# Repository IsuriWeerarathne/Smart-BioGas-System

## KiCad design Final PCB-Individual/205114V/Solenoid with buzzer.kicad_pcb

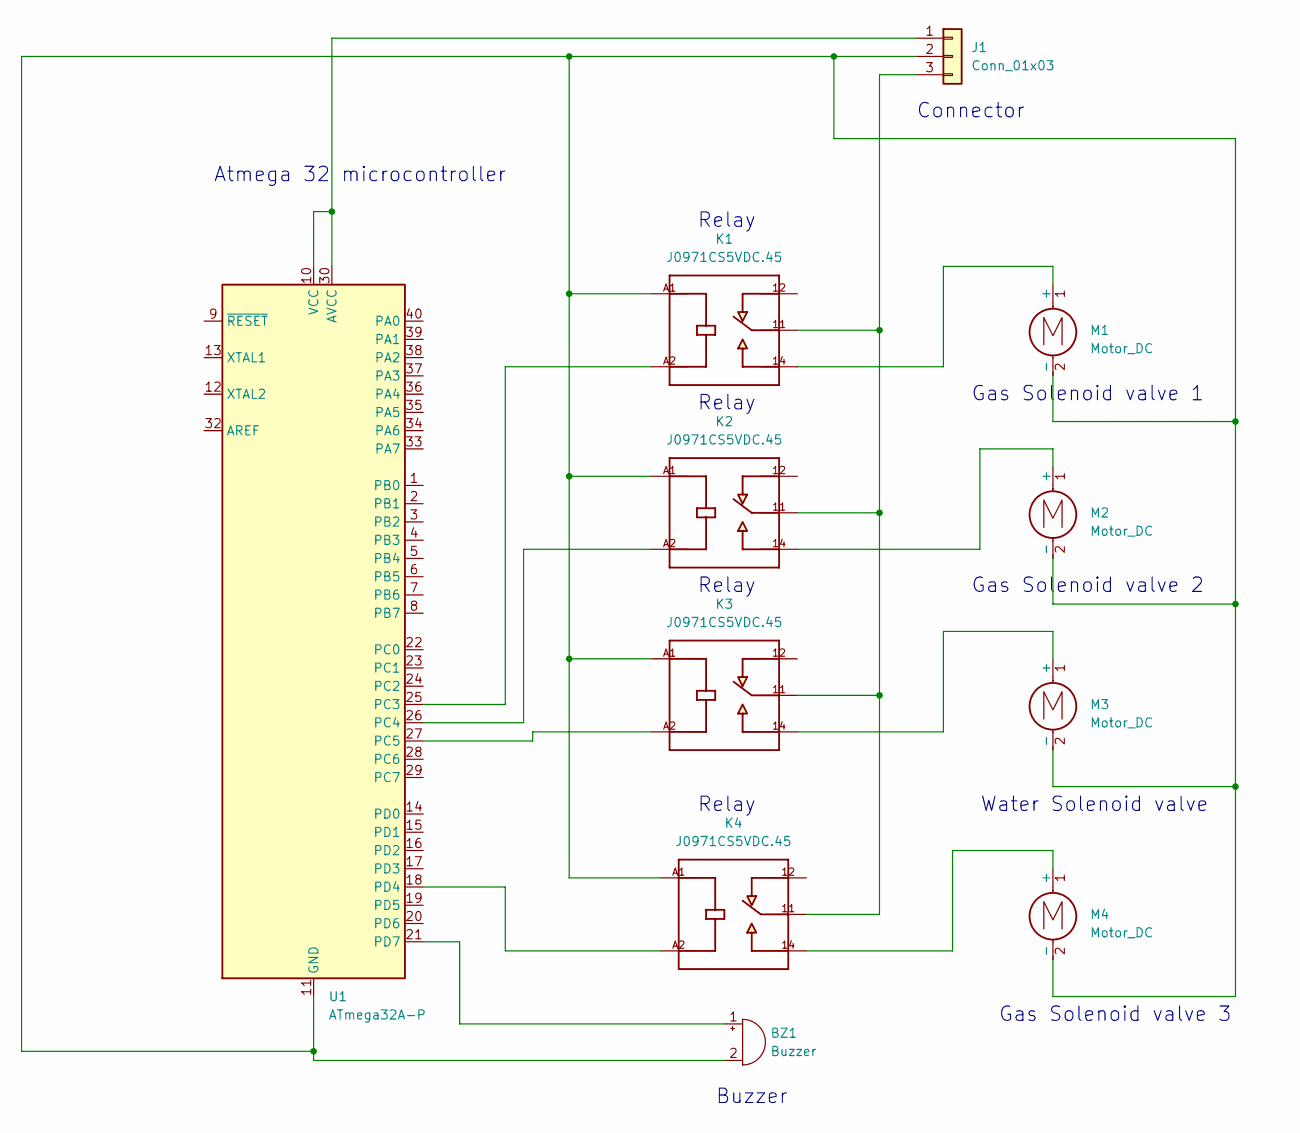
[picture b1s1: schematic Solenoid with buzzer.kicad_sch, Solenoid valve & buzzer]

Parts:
BZ1: Buzzer; Buzzer_12x9.5RM7.6
J1: Conn_01x03; PinHeader_1x03_P2.54mm_Vertical
K1, K2, K3, K4: J0971CS5VDC.45; RELAY_J0971CS5VDC.45; PARTREV --
M1, M2, M3, M4: Motor_DC; Buzzer_15x7.5RM7.6
U1: ATmega32A-P; DIP-40_W15.24mm

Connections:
unnamed: BZ1.1 (-), U1.21 (PD7)
unnamed: BZ1.2 (+), J1.2, K1.A1, K2.A1, K3.A1, K4.A1, M1.2 (-), M2.2 (-), M3.2 (-), M4.2 (-), U1.11 (GND), U1.31 (GND)
unnamed: J1.1, U1.10 (VCC), U1.30 (AVCC)
unnamed: J1.3, K1.11, K2.11, K3.11, K4.11
unnamed: K1.14, M1.1 (+)
unnamed: K1.A2, U1.25 (PC3)
unnamed: K2.14, M2.1 (+)
unnamed: K2.A2, U1.26 (PC4)
unnamed: K3.14, M3.1 (+)
unnamed: K3.A2, U1.27 (PC5)
unnamed: K4.14, M4.1 (+)
unnamed: K4.A2, U1.18 (PD4)

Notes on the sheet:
Relay
Water Solenoid valve
Gas Solenoid valve 3
Connector
Atmega 32 microcontroller
Gas Solenoid valve 2
Gas Solenoid valve 1
Buzzer

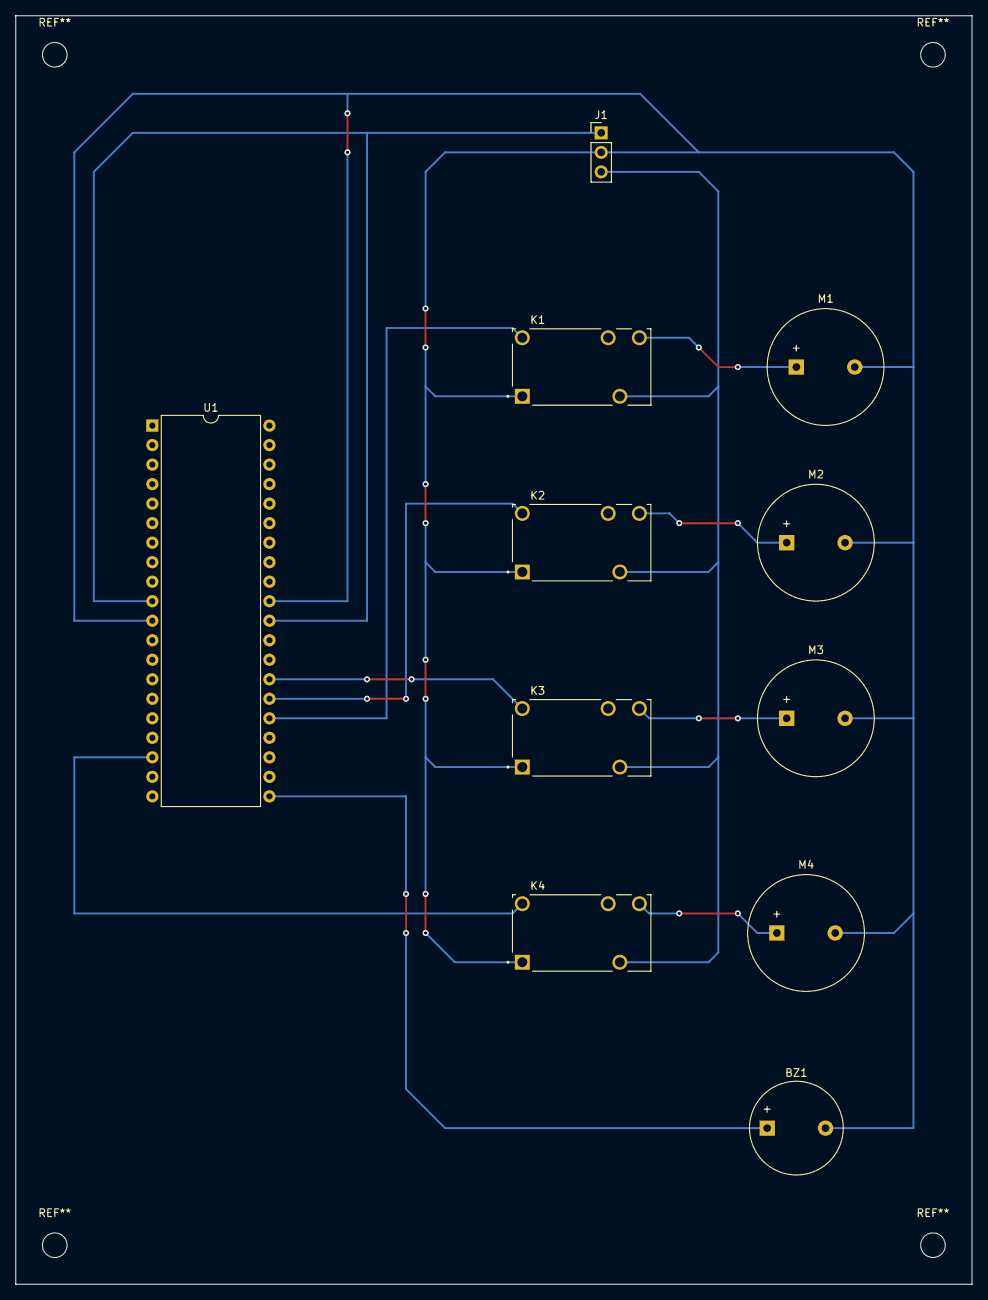
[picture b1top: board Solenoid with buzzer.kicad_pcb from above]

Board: 2 copper layers, 124.5 x 165.1 mm, 11 parts (0 on the bottom side), 12 nets.

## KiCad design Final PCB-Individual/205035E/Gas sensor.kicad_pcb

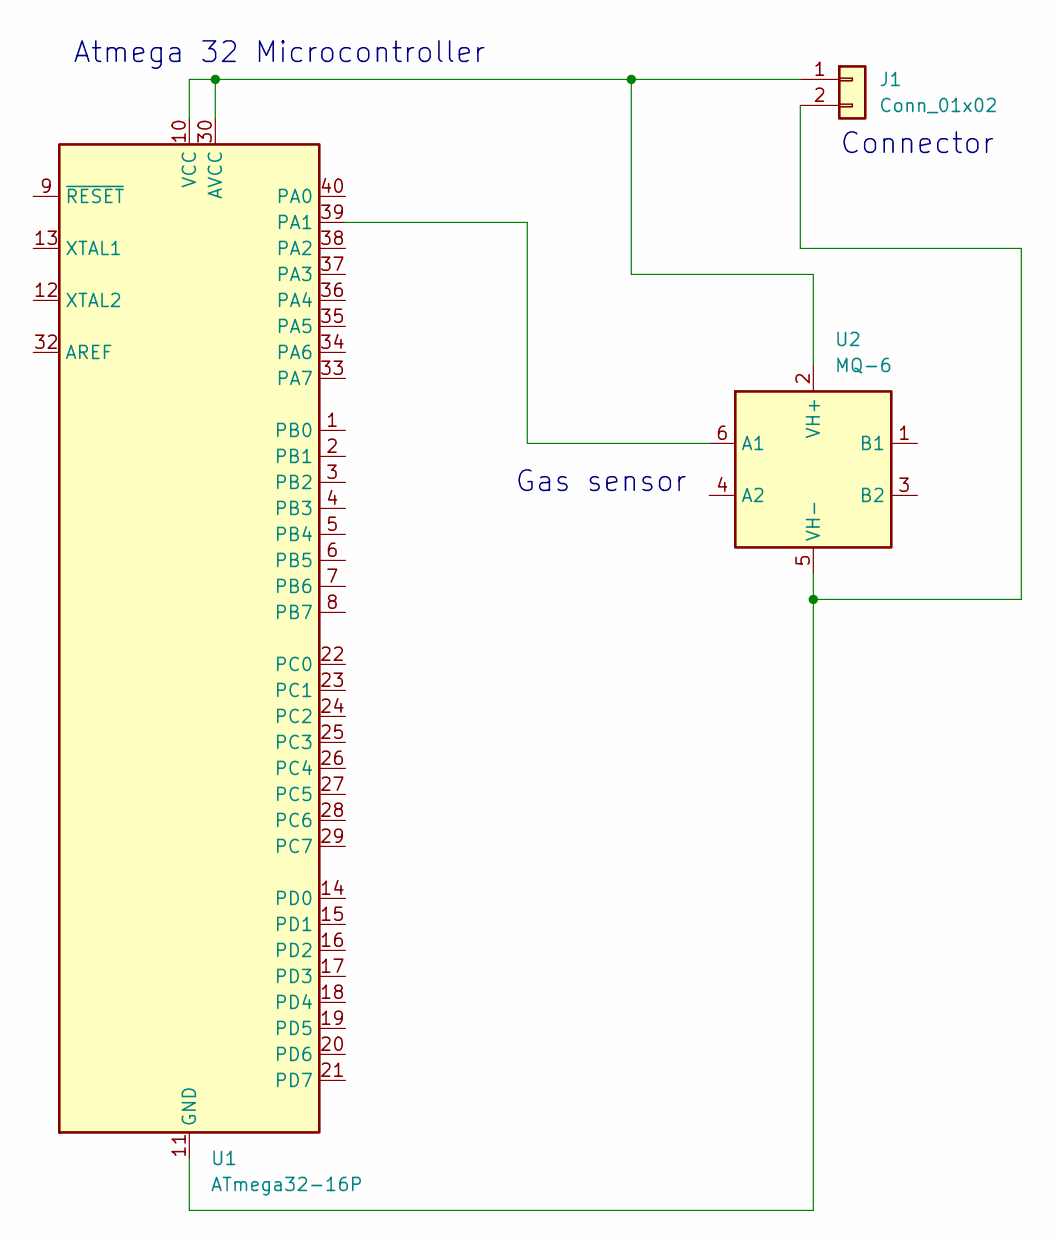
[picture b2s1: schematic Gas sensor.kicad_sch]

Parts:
J1: Conn_01x02; PinHeader_1x03_P2.54mm_Vertical
U1: ATmega32-16P; DIP-40_W15.24mm
U2: MQ-6

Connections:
unnamed: J1.1, U1.10 (VCC), U1.30 (AVCC), U2.2 (VH+)
unnamed: J1.2, U1.11 (GND), U1.31 (GND), U2.5 (VH-)
unnamed: U1.39 (PA1), U2.6 (A1)

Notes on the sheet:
Gas sensor
Atmega 32 Microcontroller
Connector

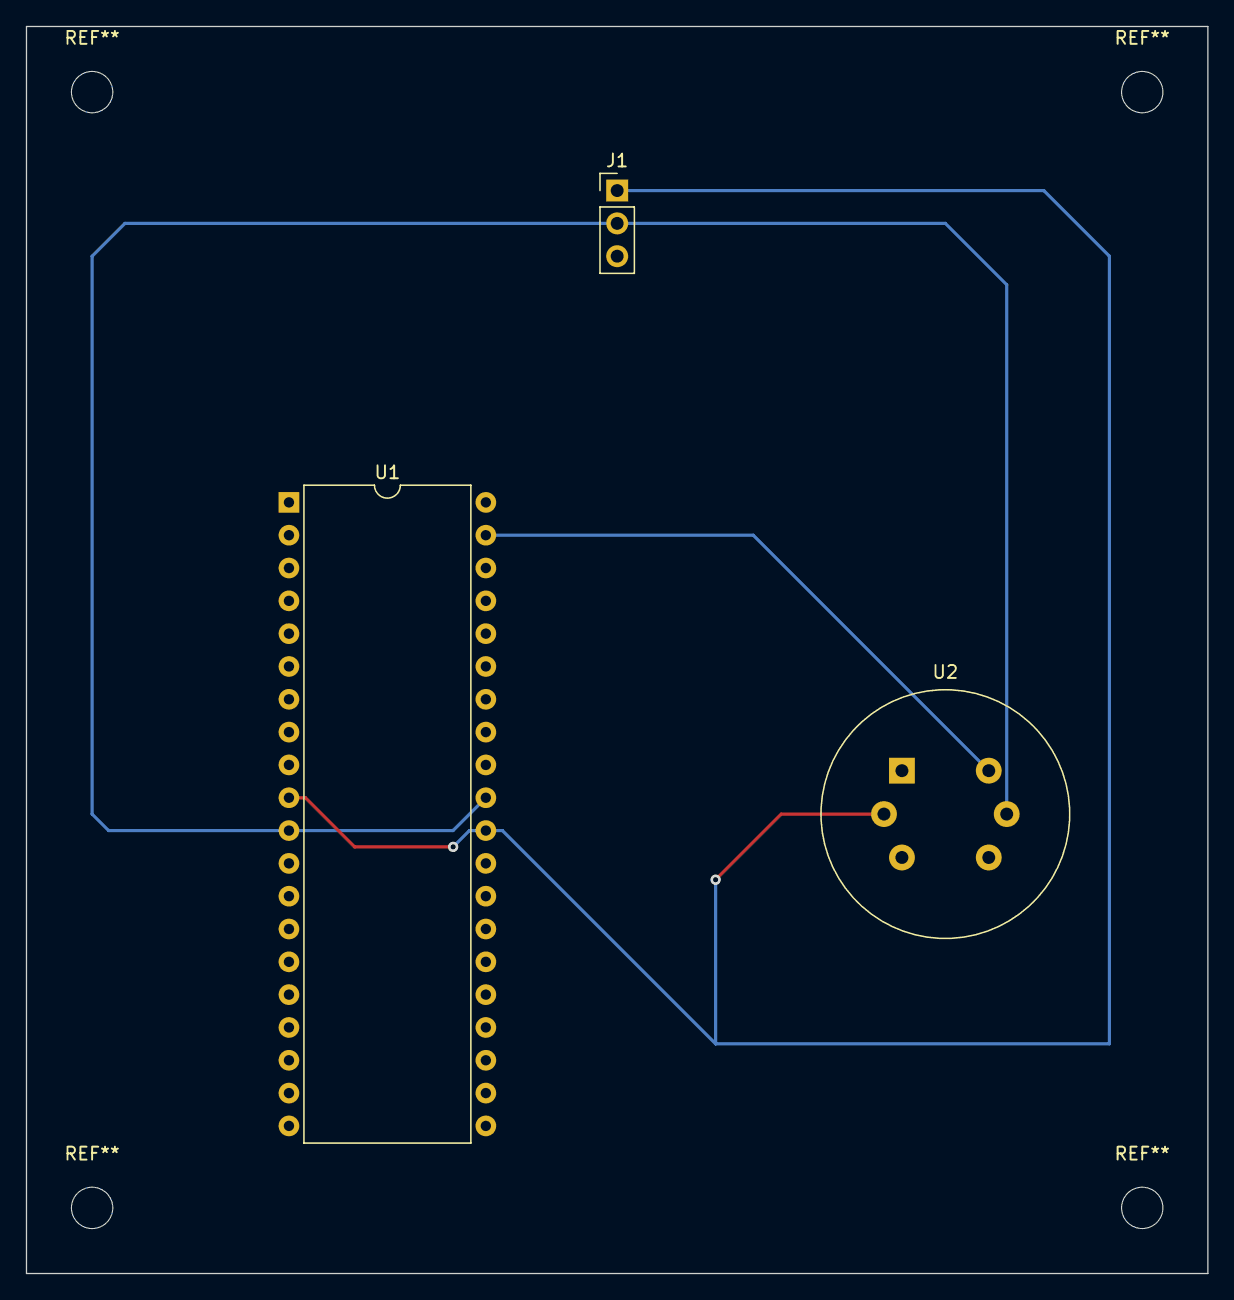
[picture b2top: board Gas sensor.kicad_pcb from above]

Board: 2 copper layers, 91.4 x 96.5 mm, 3 parts (0 on the bottom side), 3 nets.

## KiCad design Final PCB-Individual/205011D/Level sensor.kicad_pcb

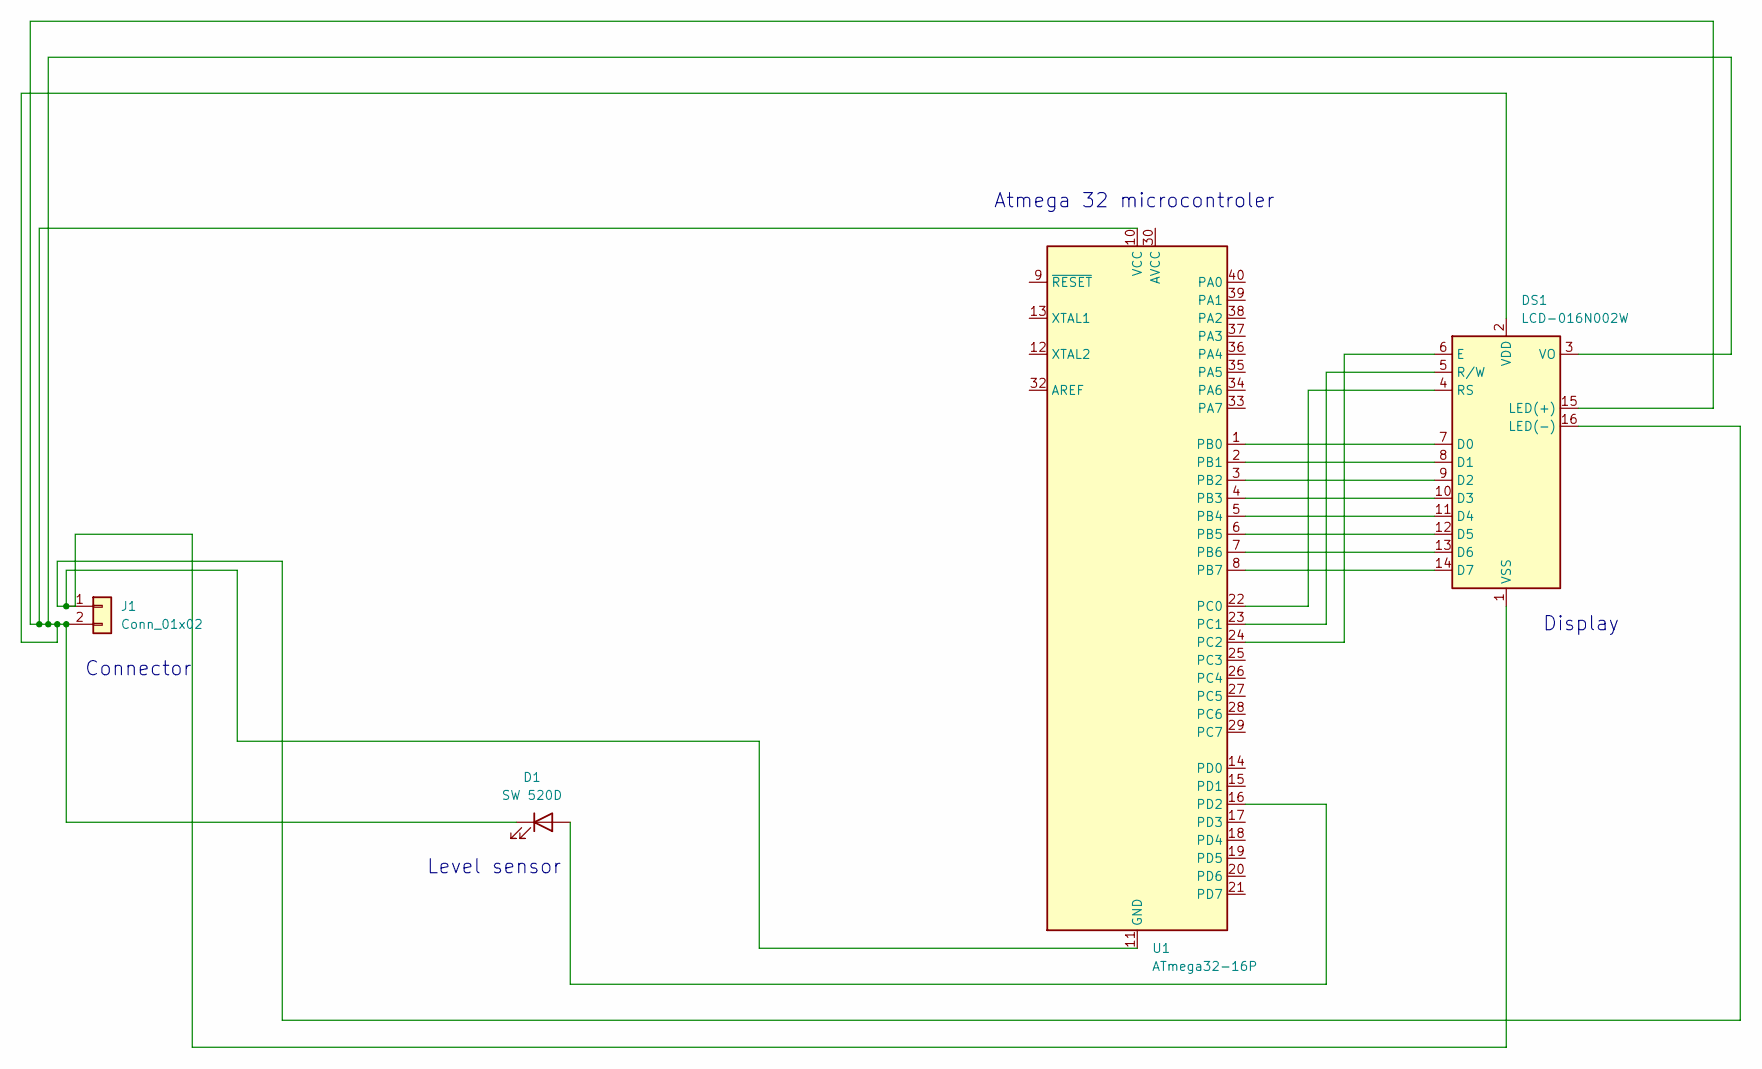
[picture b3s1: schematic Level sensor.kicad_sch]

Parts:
D1: SW 520D; LED_D5.0mm_Clear
DS1: LCD-016N002W; WC1602A
J1: Conn_01x02; PinHeader_1x02_P2.54mm_Vertical
U1: ATmega32-16P; DIP-40_W15.24mm

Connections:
unnamed: D1.1 (K), DS1.2 (VDD), DS1.3 (VO), DS1.15 (LED(+)), J1.2, U1.10 (VCC)
unnamed: DS1.1 (VSS), DS1.16 (LED(-)), J1.1, U1.11 (GND), U1.31 (GND)
unnamed: DS1.7 (D0), U1.1 (PB0)
unnamed: DS1.8 (D1), U1.2 (PB1)
unnamed: DS1.9 (D2), U1.3 (PB2)
unnamed: DS1.10 (D3), U1.4 (PB3)
unnamed: DS1.11 (D4), U1.5 (PB4)
unnamed: DS1.12 (D5), U1.6 (PB5)
unnamed: DS1.13 (D6), U1.7 (PB6)
unnamed: DS1.14 (D7), U1.8 (PB7)
unnamed: D1.2 (A), U1.16 (PD2)
unnamed: DS1.4 (RS), U1.22 (PC0)
unnamed: DS1.5 (R/W), U1.23 (PC1)
unnamed: DS1.6 (E), U1.24 (PC2)

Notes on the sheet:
Level sensor
Atmega 32 microcontroler
Connector
Display

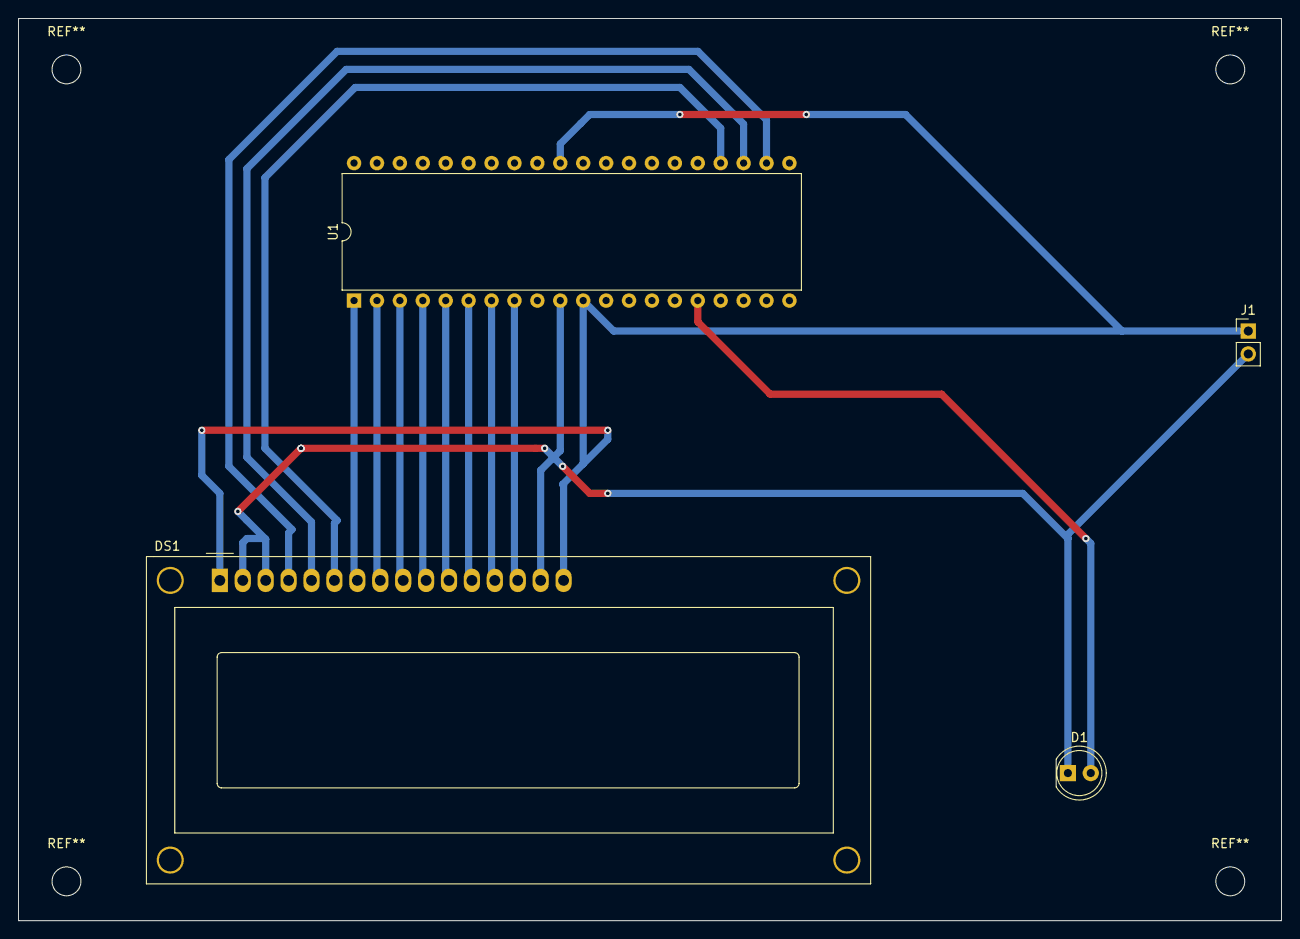
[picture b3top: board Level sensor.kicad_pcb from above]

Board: 2 copper layers, 140.0 x 100.0 mm, 4 parts (0 on the bottom side), 14 nets.

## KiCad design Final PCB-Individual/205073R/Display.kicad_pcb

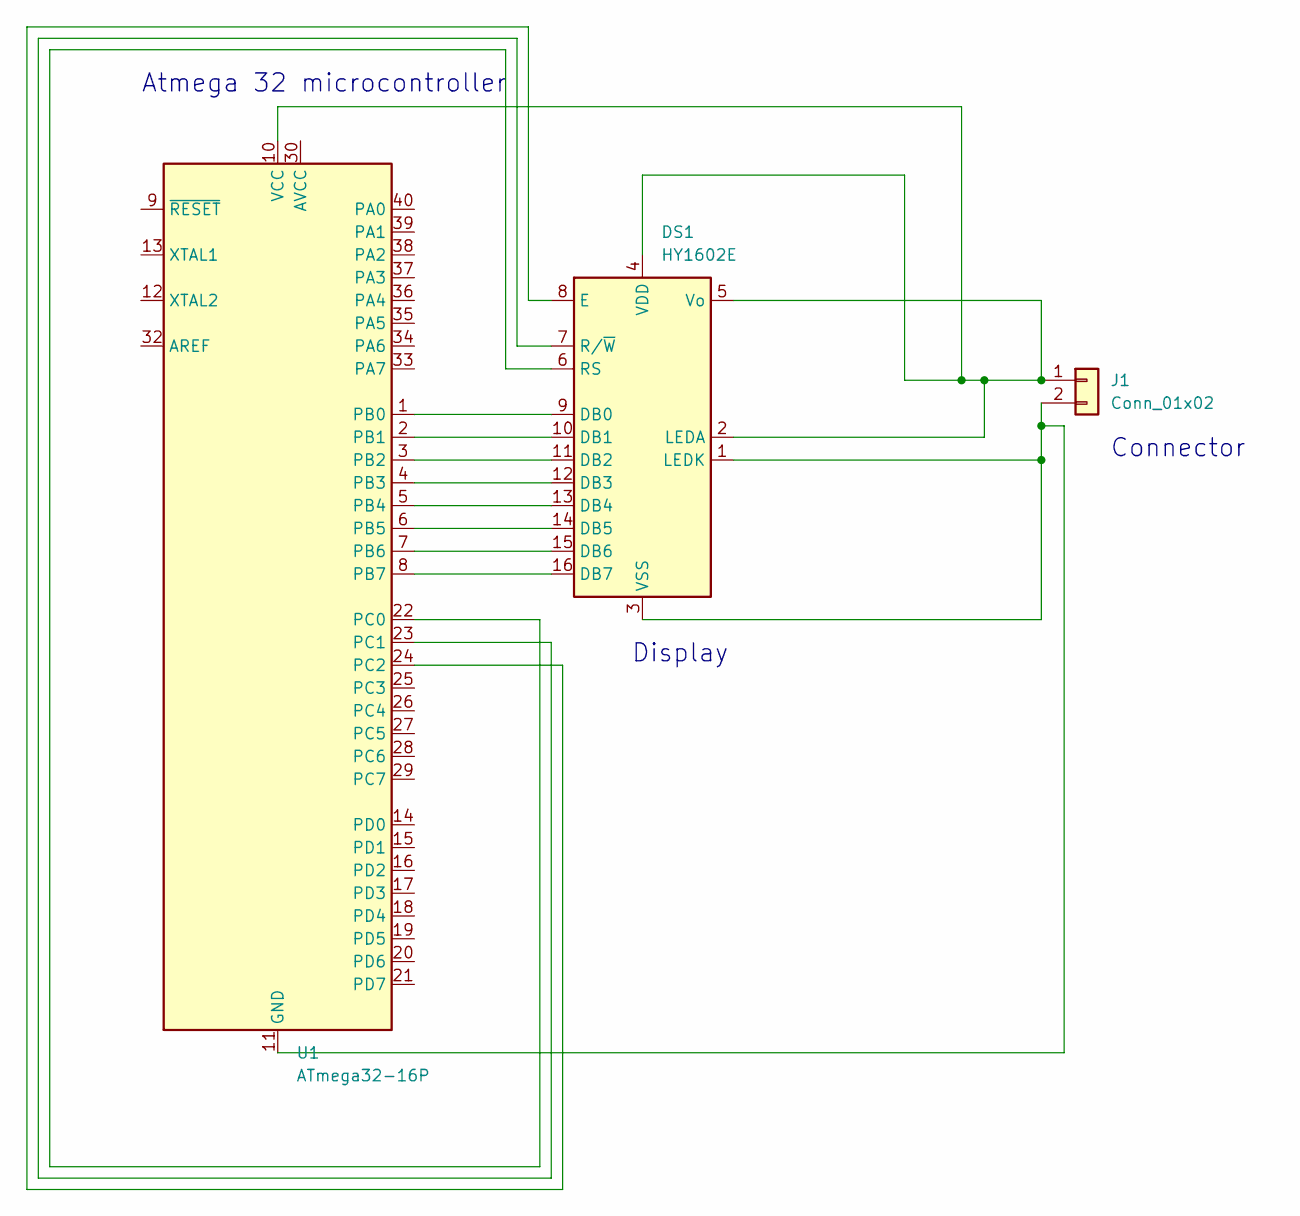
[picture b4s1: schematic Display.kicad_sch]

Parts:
DS1: HY1602E
J1: Conn_01x02; PinHeader_1x02_P2.54mm_Vertical
U1: ATmega32-16P; DIP-40_W15.24mm

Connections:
unnamed: DS1.1 (LEDK), DS1.3 (VSS), J1.2, U1.11 (GND), U1.31 (GND)
unnamed: DS1.2 (LEDA), DS1.4 (VDD), DS1.5 (Vo), J1.1, U1.10 (VCC)
unnamed: DS1.6 (RS), U1.22 (PC0)
unnamed: DS1.7 (R/~W), U1.23 (PC1)
unnamed: DS1.8 (E), U1.24 (PC2)
unnamed: DS1.9 (DB0), U1.1 (PB0)
unnamed: DS1.10 (DB1), U1.2 (PB1)
unnamed: DS1.11 (DB2), U1.3 (PB2)
unnamed: DS1.12 (DB3), U1.4 (PB3)
unnamed: DS1.13 (DB4), U1.5 (PB4)
unnamed: DS1.14 (DB5), U1.6 (PB5)
unnamed: DS1.15 (DB6), U1.7 (PB6)
unnamed: DS1.16 (DB7), U1.8 (PB7)

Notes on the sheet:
Connector
Display
Atmega 32 microcontroller

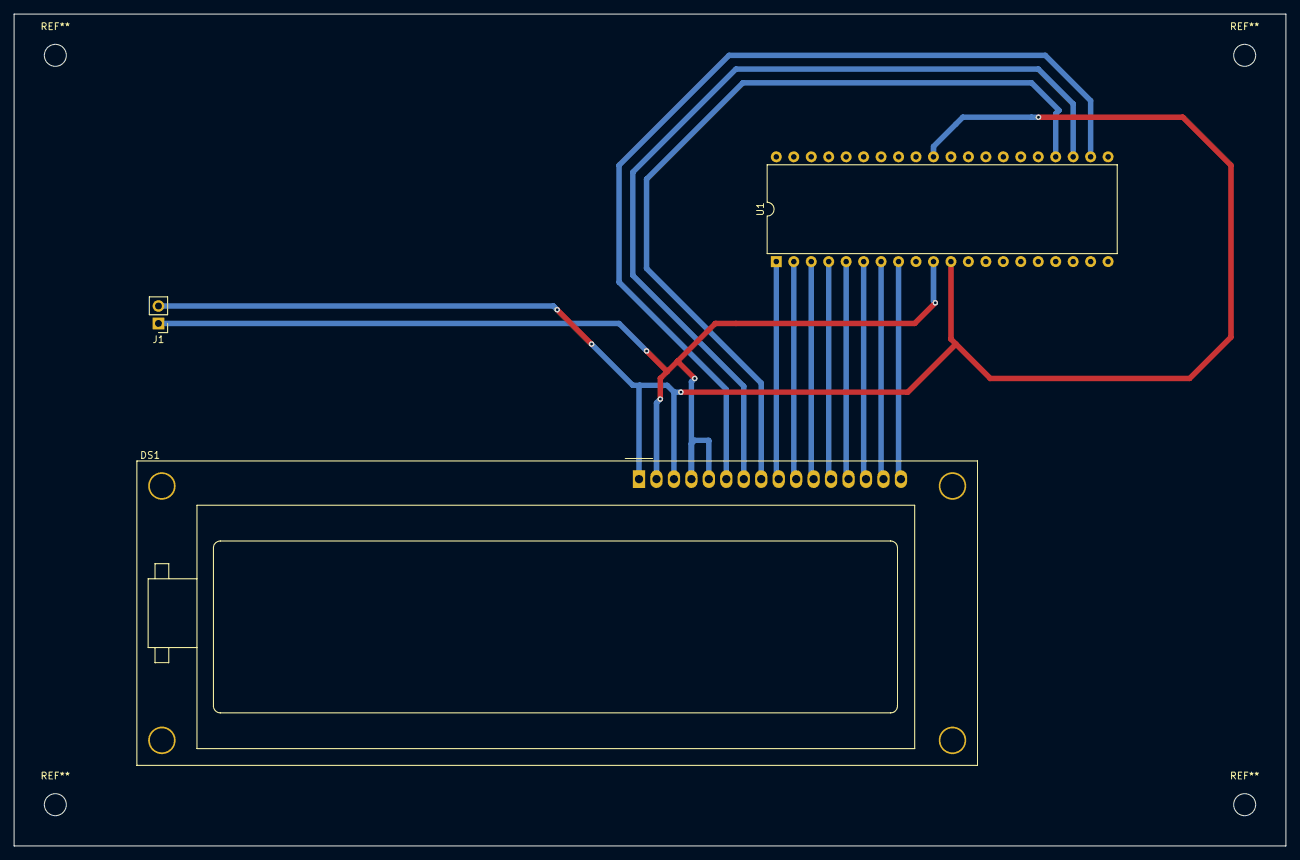
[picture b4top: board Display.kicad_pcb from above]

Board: 2 copper layers, 185.0 x 121.0 mm, 3 parts (0 on the bottom side), 13 nets.

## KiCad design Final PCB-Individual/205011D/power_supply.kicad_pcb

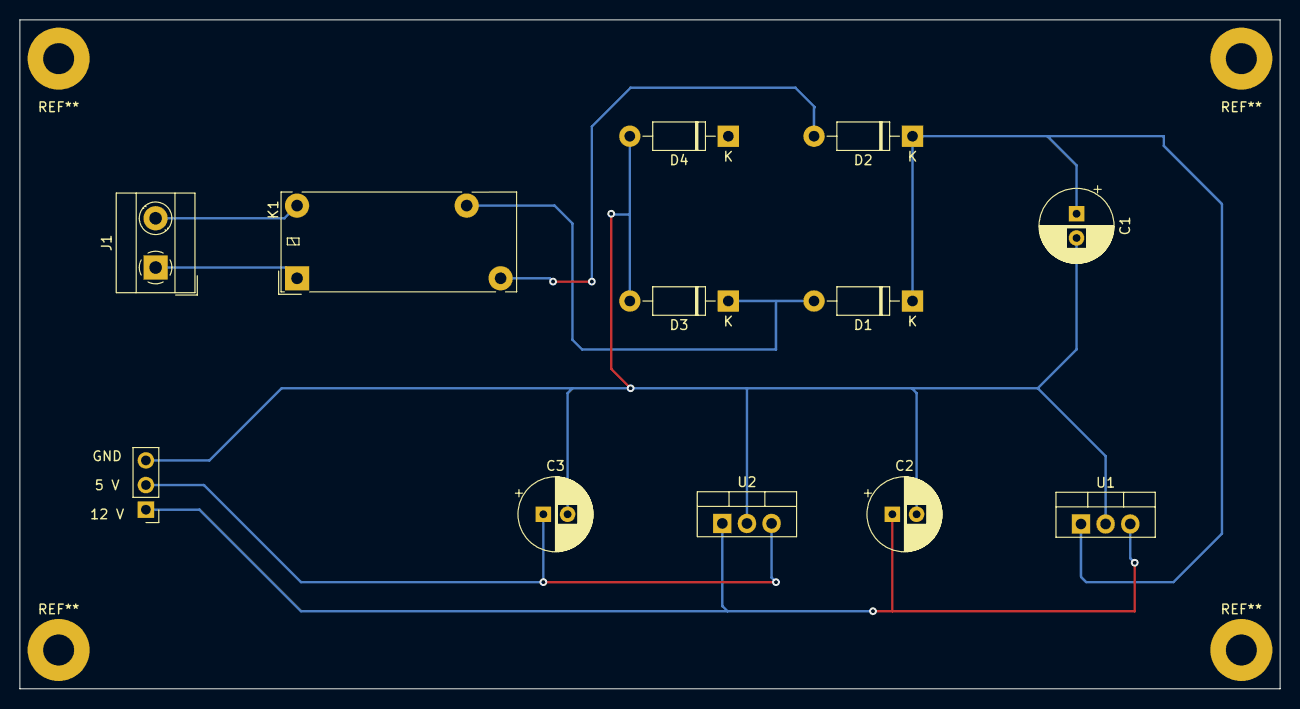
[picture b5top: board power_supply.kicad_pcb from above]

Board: 2 copper layers, 130.0 x 69.0 mm, 12 parts (0 on the bottom side), 8 nets.

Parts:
12 V: Conn_01x03; PinHeader_1x03_P2.54mm_Vertical
C1, C2, C3: C_Polarized; CP_Radial_D7.5mm_P2.50mm
D1, D2, D3, D4: 1N4007; D_DO-41_SOD81_P10.16mm_Horizontal
J1: Screw_Terminal_01x02; TerminalBlock_MetzConnect_Type101_RT01602HBWC_1x02_P5.08mm_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
K1: Transfomer; Relay_1P1T_NO_10x24x18.8mm_Panasonic_ADW11xxxxW_THT
U1: L7812; TO-220-3_Vertical
U2: L7805; TO-220-3_Vertical

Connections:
unnamed: 12 V.2, C3.1, U2.3 (OUT)
unnamed: C1.1, D1.1 (K), D2.1 (K), U1.1 (IN)
unnamed: D1.2 (A), D3.1 (K), K1.5
unnamed: D2.2 (A), K1.3
unnamed: 12 V.3, C1.2, C2.2, C3.2, D3.2 (A), D4.2 (A), U1.2 (GND), U2.2 (GND)
unnamed: J1.1, K1.1
unnamed: J1.2, K1.6
unnamed: 12 V.1, C2.1, U1.3 (OUT), U2.1 (IN)

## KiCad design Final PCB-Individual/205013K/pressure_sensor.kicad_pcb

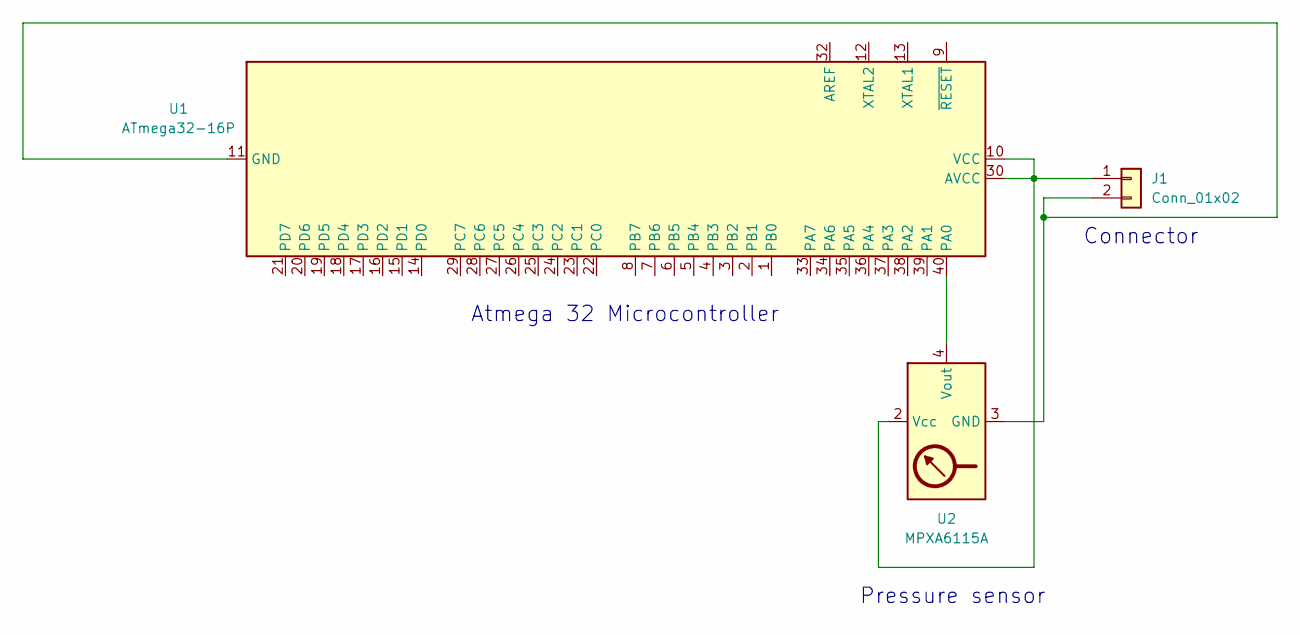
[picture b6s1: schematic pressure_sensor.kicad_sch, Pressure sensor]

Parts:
J1: Conn_01x02; PinHeader_1x02_P2.54mm_Vertical
U1: ATmega32-16P; DIP-40_W15.24mm
U2: MPXA6115A; Freescale_98ARH99066A

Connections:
unnamed: J1.1, U1.10 (VCC), U1.30 (AVCC), U2.2 (Vcc)
unnamed: J1.2, U1.11 (GND), U1.31 (GND), U2.3 (GND)
unnamed: U1.40 (PA0), U2.4 (Vout)

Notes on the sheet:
Connector
Atmega 32 Microcontroller
Pressure sensor

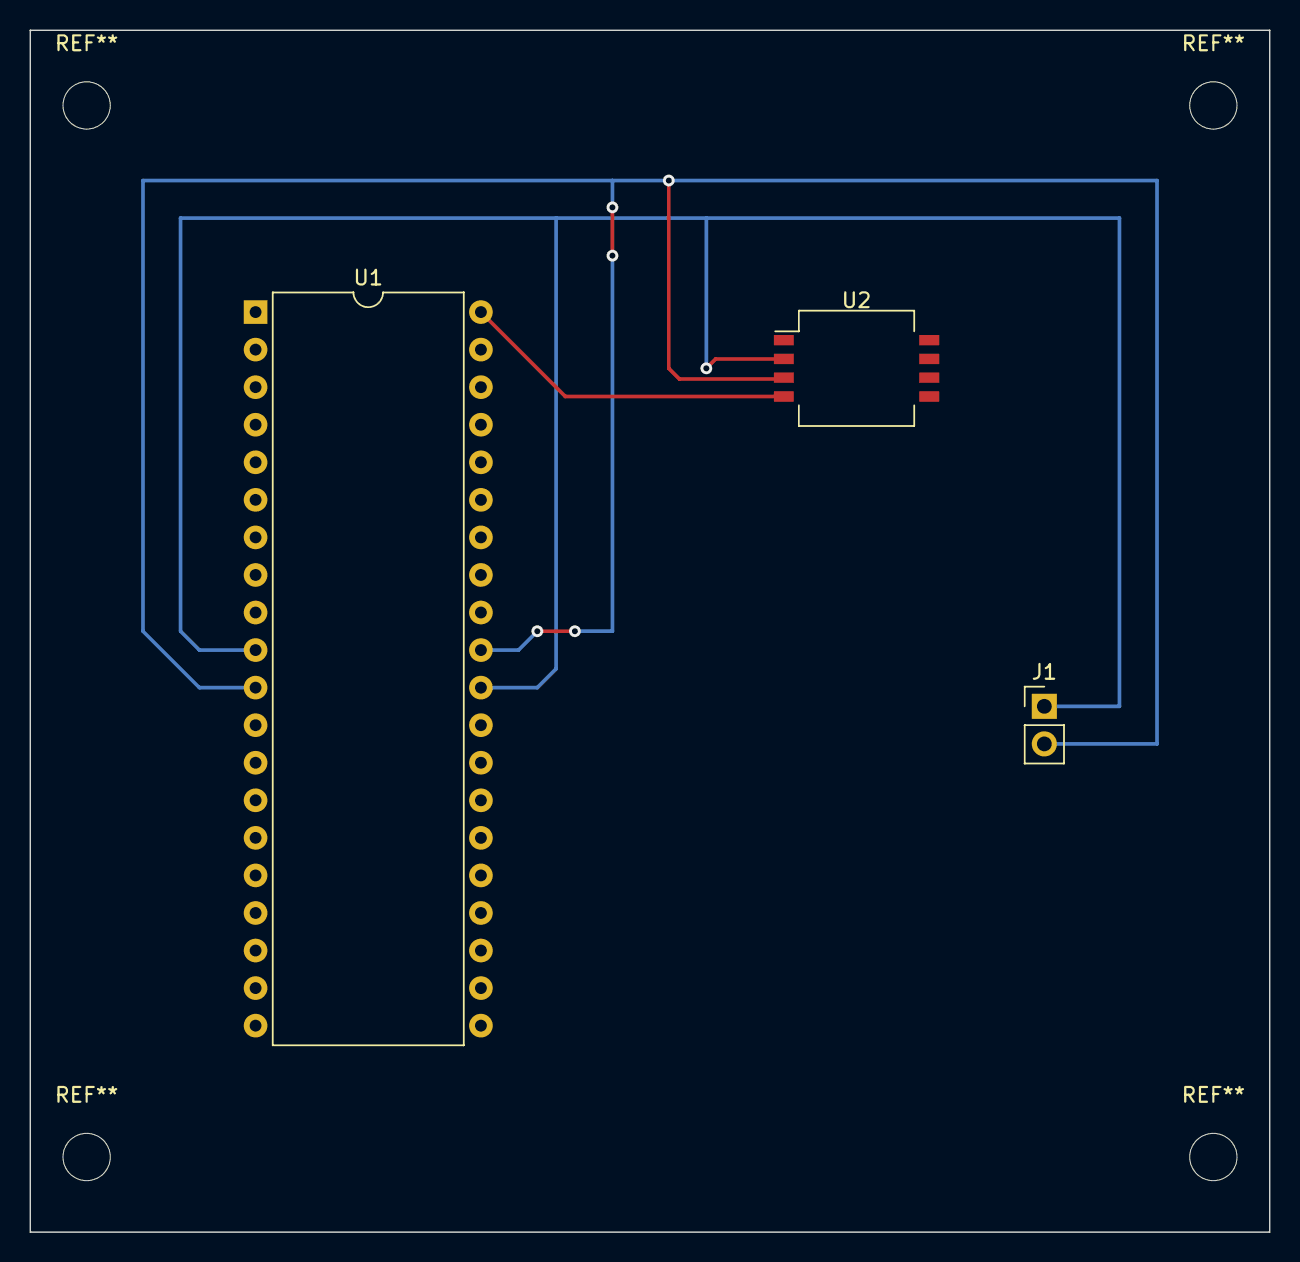
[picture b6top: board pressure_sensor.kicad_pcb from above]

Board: 2 copper layers, 83.8 x 81.3 mm, 3 parts (0 on the bottom side), 3 nets.

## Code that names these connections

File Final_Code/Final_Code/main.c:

#define F_CPU 16000000UL
#include <avr/io.h>
#include <util/delay.h>
#include <string.h>
#include <stdio.h>
#include "LCD_16x2_H_file.h"


void ADC_Init(){
	DDRA &= ~(1<<PA0);								/* Make ADC port pin 0 as input */
	ADCSRA = 0x87;									/* Enable ADC, with freq/128  */
	ADMUX = 0x40;									/* Vref: Avcc, ADC channel: 0 */
}

int ADC_Read(char channel)
{
	ADMUX = 0x40 | (channel & 0x07);				/* set input channel to read */
	ADCSRA |= (1<<ADSC);							/* Start ADC conversion */
	while (!(ADCSRA & (1<<ADIF)));					/* Wait until end of conversion by polling ADC interrupt flag */
	ADCSRA |= (1<<ADIF);							/* Clear interrupt flag */
	_delay_ms(1);									/* Wait a little bit */
	return ADCW;									/* Return ADC word */
}


void ADC_Init1(){
	DDRA &= ~(1<<PA1); 							    /* Make ADC port pin 1 as input */
	ADCSRA = 0x87;									/* Enable ADC, with freq/128  */
	/* Vref: Avcc, ADC channel: 0 */
}

int ADC_Read1()
{
	ADMUX = 0x41;									/* set input channel to read */
	ADCSRA |= (1<<ADSC);							/* Start ADC conversion */
	while (!(ADCSRA & (1<<ADIF)));					/* Wait until end of conversion by polling ADC interrupt flag */
	ADCSRA |= (1<<ADIF);							/* Clear interrupt flag */
	_delay_ms(1);									/* Wait a little bit */
	return ADCW;									/* Return ADC word */
}

//define values to calculate PPM (line 51 to 54) curve points

float b_of_lpg=1.25;
float m_of_lpg=-0.45;
float b_of_Methane=1.34;
float m_of_Methane=-0.37;
float Mq2_Anlog_value = 0;

//level view code
void view_level(){
	LCD_Clear();
	_delay_ms(50);
	LCD_String_xy(1,0,"  liquid level ");		//Display if liquid level is high
	LCD_String_xy(2,0,"    is high");
}


int main()

{
	//Following 3 pins for button level sensor
	DDRD &= ~(1<<PD2);								//Make PD2 port as input pin for level sensor
	DDRC |= (1<<PC5);								// Make PC5 port as output pin for water solenoid valve
	DDRD &= ~(1<<PD5);								//Make PD5 port as input pin for the button to remove liquid
	
	DDRD =DDRD | (1<<4);							// turn off the solenoid valve--- Lp gas  make as output port
	DDRC = DDRC | (1<<3);							//turn off bio gas supply --- make as output port
	DDRC = DDRC | (1<<4);							//make port c solenoid valve as output to the outside
	
	DDRD &=~(1<<PD6);								// button to demontrate gas sensor
	DDRD = DDRD | (1<<7);							//make port d pin 7 as output to buzzer
	
	
	char pressure[10];
	float kiloPaskal;

	LCD_Init();										/* initialize 16x2 LCD*/
	ADC_Init();										/* initialize ADC*/
	
	
	while(1)
	{
			LCD_Clear();
		    LCD_String_xy(1,2,"SMART BIO GAS");
		    LCD_String_xy(2,5,"SYSTEM");
		    _delay_ms(300);
		    LCD_Clear();

		//Code lines for buton to remove liquid
		
		if (PIND & (1<<PD5))
		{
			_delay_ms(50);
			PORTC |= (1<<PC5);
			}else{
			_delay_ms(50);
			PORTC &= ~(1<<PC5);
		}
		
		
		kiloPaskal = (ADC_Read(0)*4.88);
		kiloPaskal = ((((kiloPaskal+0.3)/255)-0.04)/0.009);		//calculate pressure
		_delay_ms(1000);
		memset(pressure,0,10);
		
		
		if (kiloPaskal>=1581)									//When bio gas pressure goes high
		{
			if (PIND & (1<<PD2))								//to display level out and gas in use
			{
				view_level();
				}else{
				LCD_Clear();
				_delay_ms(50);
				LCD_String_xy(1,0,"    Biogas go");
				LCD_String_xy(2,0,"     outside");
			}
			
			PORTC |=(1<<PC3);									//Turn on bia gas supply
			PORTC |=(1<<PC4);									//turn on bio gas output(to outside) solenoid valve
			PORTD &=~(1<<PD4);									//Turn off LP gas supply
			
		}else if (kiloPaskal>=400)
		{
			if (PIND & (1<<PD2))
			{
				view_level();
				}else{
				LCD_Clear();
				_delay_ms(50);
				LCD_String_xy(1,0,"     Biogas");
				LCD_String_xy(2,0,"     in use");
			}
			
			PORTC &=~(1<<PC4);									//turn off bio output sol
			PORTC |=(1<<PC3);									//Turn on bia gas supplyenoid valve
			PORTD &=~(1<<PD4);									//Turn off LP gas supply
			}else{
			if (PIND & (1<<PD2))
			{
				view_level();
				}else{
				LCD_Clear();
				_delay_ms(50);
				LCD_String_xy(1,0,"      LPgas");
				LCD_String_xy(2,0,"     in use");
			}
			
			PORTC &=~(1<<PC3);								//Turn off bio gas supply
			PORTD |=(1<<PD4);								//Turn on Lp gas supply
			PORTC &=~(1<<PC4);								//turn off bio output solenoid valve
		}
		


		//close all the solenoid valves --- to show the work of gas sensor
		if (PINA & (1<<PA1))
		{
			LCD_Clear();
			PORTC &=~(1<<PC3);									//Turn off bio gas supply
			PORTC &=~(1<<PC4);									//turn off bio output solenoid valve
			PORTD &=~(1<<PD4);									//Turn off LP gas supply
			PORTD |= (1<<PD7);									//Turn on the buzzer
			
			LCD_String_xy(1,0,"*** Gas leak ***");
			_delay_ms(100);
			}else{
			PORTD &= ~(1<<PD7);									//Turn off the buzzer
		}
		
		
		//	gas sensor up to line 224 // commented beacues  gas sensor is not working in protues
		
				ADC_Init1();
		 		_delay_ms(1000);
		 		float ADC_input_mq2 = ADC_Read(1);							//get the ADC pin 1 input
		
		 		for (int x=0;x<20;x++)
		 		{
					float Mq2_Anlog_value = ADC_input_mq2/20;				//take analog average readings from the sensor until stable
		 			return Mq2_Anlog_value;
		 		}
		 		Mq2_Anlog_value = Mq2_Anlog_value/20;
		 		float Mq2_V_Volts = (Mq2_Anlog_value *5)/1023;				//161 line & this line to convert analog input to voltage
		 		float RS_of_Air = (5-Mq2_V_Volts)/Mq2_V_Volts;				//Take RS of the air
		 		float RO = RS_of_Air/9.8;
		 		_delay_ms(50);
		
		 		float RS_RO_Ratio = RS_of_Air/ RO;
		 		float PPM_Log_lpg = (log(RS_RO_Ratio)-b_of_lpg)/m_of_lpg;	//getting PPM value in log for LPG
		 		float PPM_Log_methane = (log(RS_RO_Ratio)-b_of_Methane)/m_of_Methane; //getting PPM value in log for methane
		
		 		float PPM_L =  pow(10,PPM_Log_lpg);							//get the inverse of the log value to find the real values
		 		float PPM_M =  pow(10,PPM_Log_methane);						//get the inverse of the log value to find the real values
		
		//Wrote condition based on assumptions
		
		 		if (PPM_L > 2000) //assume if lpg goes higher than 2000 it is danger
		 		{
		 			PORTC &=~(1<<PC3);										//Turn off bio gas supply
		 			PORTC &=~(1<<PC4);										//turn off bio output solenoid valve
		 			PORTD &=~(1<<PD4);										//Turn off LP gas supply
		 			PORTD |= (1<<PD7);										//Turn on the buzzer
		 			LCD_Clear();
		 			LCD_String_xy(1,0,"Gas leak -LPG");
		 			_delay_ms(100);
		
		 		}else if (PPM_M > 1000)										//assume if Methane goes higher than 1000 it is danger
		 		{
		 			PORTC &=~(1<<PC3);										//Turn off bio gas supply
		 			PORTC &=~(1<<PC4);										//turn off bio output solenoid valve
		 			PORTD &=~(1<<PD4);										//Turn off LP gas supply
					PORTD |= (1<<PD7);										//Turn on the buzzer
		 			LCD_Clear();
		 			LCD_String_xy(1,0,"Gas leak -Methane");
		 			_delay_ms(100);
		
		 		}else{
		 			PORTD &= ~(1<<PD7);										//Turn off the buzzer
		 		}
		

		
		
	}
	


	
	return 0;
}
